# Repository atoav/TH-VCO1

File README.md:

# TH-VCO1

This is a fork based on [the Eurorack Layout Tom Whitwell]( http://www.birthofasynth.com/Thomas_Henry/Pages/VCO-1.html) Oscillator published for the [Thomas Henry VCO 1](http://www.birthofasynth.com/Thomas_Henry/Pages/VCO-1.html) Oscillator.

**NB: All rights to this design rest with Thomas Henry. I do not claim or grant any copyright or license to this design. This is the outcome of an University course at HFBK Hamburg. A limited run of 100 pieces has been produced, which will be sold. We are not allowed to share CAD files of the circuit as "Thomas Henry prefers that all hardware for my designs come from Fonik only, and that schematics for his designs come from Scott and E-M". I will take this page down if he asks me to.** 

## Changes

Compared to Tom's Layout some things changed:

- the complete panel layout has been changed for a fancier (and imho a bit more easier to grasp) layout
- The board-pot has been completely rerouted and is now a single layer board (the bottom layer is a nice, undivided ground plane)
- Two 1x5 Header Pin Strips have been added (this could potentially help to save the screws and add mechanical stability)
- All Resistor Pads have been swapped for square pads
- The PWM CV Attenuator Pot is now a 9mm Alpha trimmer (the small ones with the plastic head, commonly used for attenuverters)
- Cleaned up traces and silkscreen where necessary

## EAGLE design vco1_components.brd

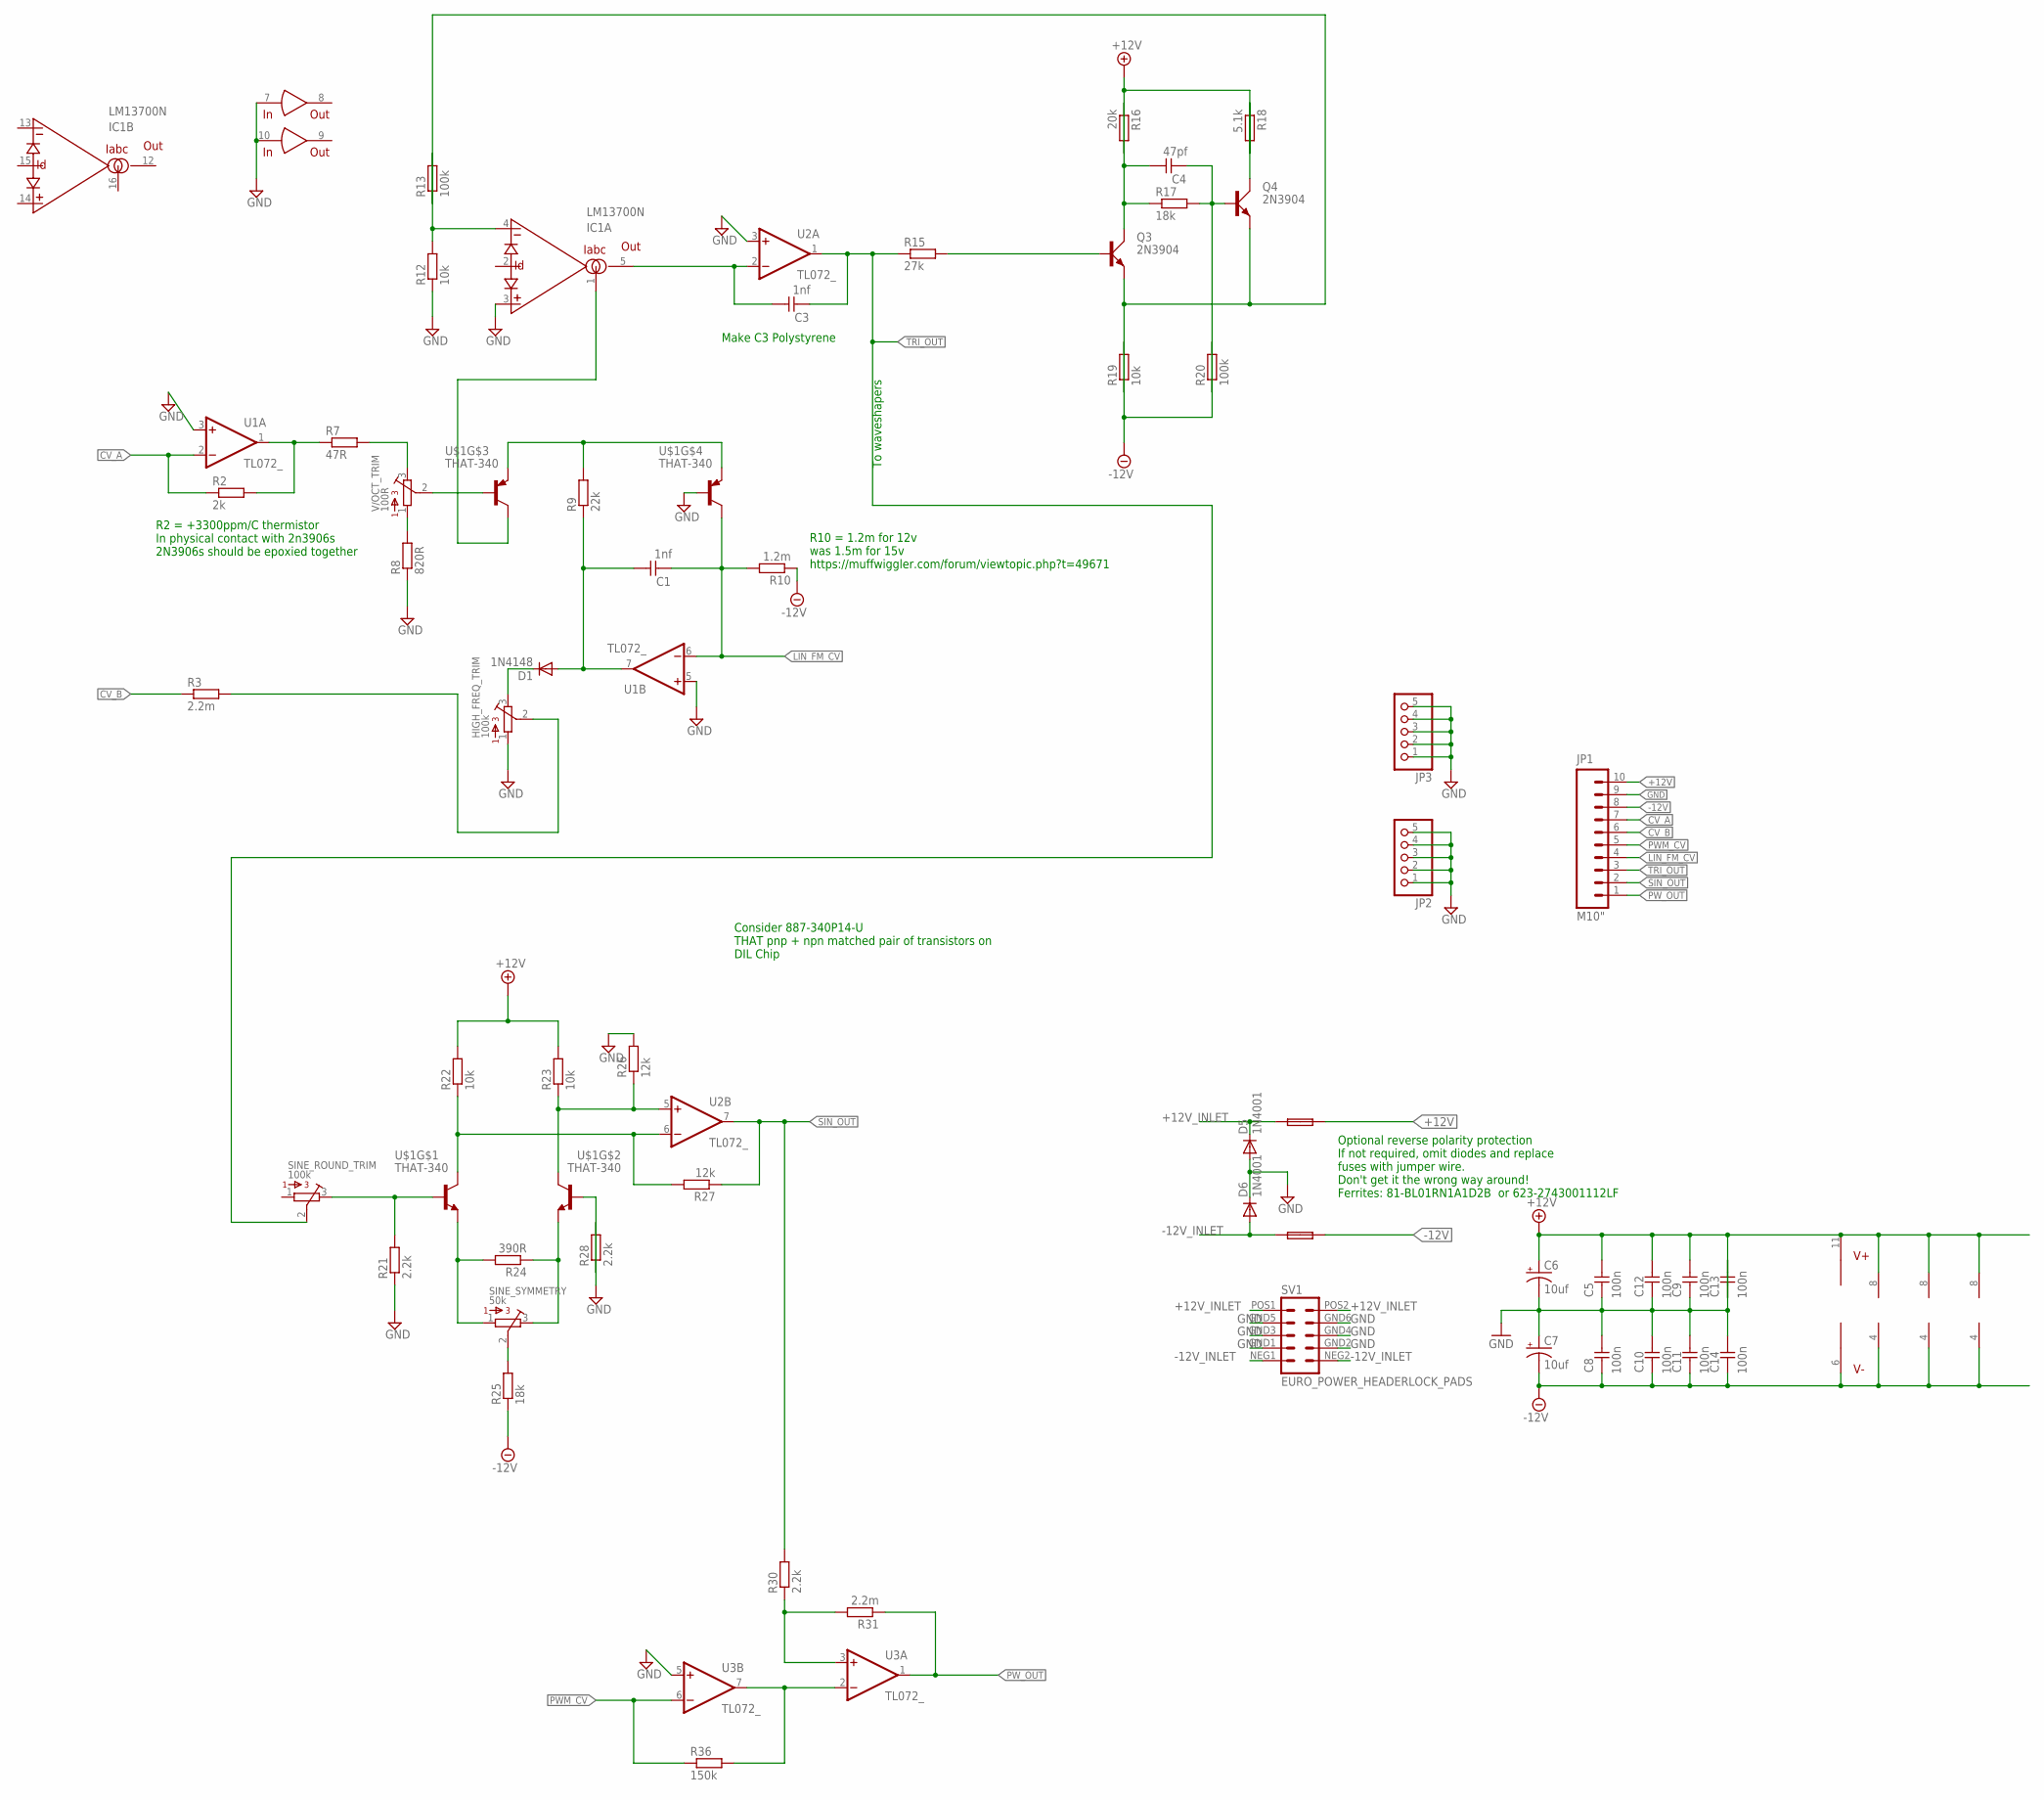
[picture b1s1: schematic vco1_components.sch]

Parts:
C1, C3: 1nf; C050-024X044
C4: 47pf; C050-024X044
C5, C8, C9, C10, C11, C12, C13, C14: 100n; C050-024X044
C6, C7: 10uf; CPOL-RADIAL-10UF-25V
D1: 1N4148; DO35-7
D5, D6: 1N4001; DO41-10
F1, F2: FUSE; C050H075X075
HIGH_FREQ_TRIM: 100k; BOURNS_3362P_TRIMMER
IC1: LM13700N; DIL16
JP1: M10"; 1X10
JP2, JP3: PINHD-1X55X2MM; 1_05X2MM
Q3, Q4: 2N3904; TO92D
R2: 2k; 7MM_RESISTOR
R3, R31: 2.2m; 7MM_RESISTOR
R7: 47R; 7MM_RESISTOR
R8: 820R; 7MM_RESISTOR
R9: 22k; 7MM_RESISTOR
R10: 1.2m; 7MM_RESISTOR
R12, R19, R22, R23: 10k; 7MM_RESISTOR
R13, R20: 100k; 7MM_RESISTOR
R15: 27k; 7MM_RESISTOR
R16: 20k; 7MM_RESISTOR
R17, R25: 18k; 7MM_RESISTOR
R18: 5.1k; 7MM_RESISTOR
R21, R28, R30: 2.2k; 7MM_RESISTOR
R24: 390R; 7MM_RESISTOR
R26, R27: 12k; 7MM_RESISTOR
R36: 150k; 7MM_RESISTOR
SINE_ROUND_TRIM: 100k; BOURNS_3362P_TRIMMER
SINE_SYMMETRY: 50k; BOURNS_3362P_TRIMMER
SV1: EURO_POWER_HEADERLOCK_PADS; EURO_PWR_HEADER_LOCK
U1, U2, U3: TL072_; DIL08
U$1: THAT-340; DIL14
V/OCT_TRIM: 100R; BOURNS_3362P_TRIMMER

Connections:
+12V: C5.1, C6.1 (+), C9.1, C12.1, C13.2, F1.2, IC1.11 (V+), JP1.10, R16.2, R18.2, R22.2, R23.2, U1.8 (V+), U2.8 (V+), U3.8 (V+)
+12V_INLET: D5.C, F1.1, SV1.POS1 (10), SV1.POS2 (9)
-12V: C7.2 (-), C8.2, C10.2, C11.2, C14.2, F2.2, IC1.6 (V-), JP1.8, R10.1, R19.2, R20.2, R25.1, U1.4 (V-), U2.4 (V-), U3.4 (V-)
-12V_INLET: D6.A, F2.1, SV1.NEG1 (2), SV1.NEG2 (1)
CV_A: JP1.7, R2.1, U1.2 (-IN)
CV_B: JP1.6, R3.1
GND: C5.2, C6.2 (-), C7.1 (+), C8.1, C9.2, C10.1, C11.1, C12.2, C13.1, C14.1, D5.A, D6.C, HIGH_FREQ_TRIM.1, IC1.3 (+IN), IC1.7 (IN), IC1.10 (IN), JP1.9, JP2.1, JP2.2, JP2.3, JP2.4, JP2.5, JP3.1, JP3.2, JP3.3, JP3.4, JP3.5, R8.1, R12.1, R21.1, R26.2, R28.2, SV1.GND1 (4), SV1.GND2 (3), SV1.GND3 (6), SV1.GND4 (5), SV1.GND5 (8), SV1.GND6 (7), U1.3 (+IN), U1.5 (+IN), U2.3 (+IN), U3.5 (+IN), U$1.9 (B)
LIN_FM_CV: C1.2, JP1.4, R10.2, U1.6 (-IN), U$1.8 (C)
unnamed: R2.2, R7.1, U1.1 (OUT)
unnamed: R7.2, V/OCT_TRIM.3
unnamed: R8.2, V/OCT_TRIM.1
unnamed: U$1.6 (B), V/OCT_TRIM.2
unnamed: R9.2, U$1.5 (E), U$1.10 (E)
unnamed: IC1.1 (IABC), U$1.7 (C)
unnamed: C1.1, D1.A, R9.1, U1.7 (OUT)
unnamed: D1.C, HIGH_FREQ_TRIM.3
unnamed: HIGH_FREQ_TRIM.2, R3.2
unnamed: IC1.4 (-IN), R12.2, R13.2
unnamed: C3.1, IC1.5 (OUT), U2.2 (-IN)
unnamed: Q3.B, R15.2
unnamed: C4.1, Q3.C, R16.1, R17.1
unnamed: R21.2, SINE_ROUND_TRIM.3, U$1.2 (B)
unnamed: C4.2, Q4.B, R17.2, R20.1
unnamed: Q4.C, R18.1
unnamed: R25.2, SINE_SYMMETRY.2
unnamed: Q3.E, Q4.E, R13.1, R19.1
unnamed: R22.1, R27.2, U2.6 (-IN), U$1.1 (C)
unnamed: R23.1, R26.1, U2.5 (+IN), U$1.14 (C)
unnamed: R24.2, SINE_SYMMETRY.1, U$1.3 (E)
unnamed: R24.1, SINE_SYMMETRY.3, U$1.12 (E)
unnamed: R28.1, U$1.13 (B)
unnamed: R30.1, R31.2, U3.3 (+IN)
unnamed: R36.2, U3.2 (-IN), U3.7 (OUT)
PWM_CV: JP1.5, R36.1, U3.6 (-IN)
PW_OUT: JP1.1, R31.1, U3.1 (OUT)
SIN_OUT: JP1.2, R27.1, R30.2, U2.7 (OUT)
TRI_OUT: C3.2, JP1.3, R15.1, SINE_ROUND_TRIM.2, U2.1 (OUT)

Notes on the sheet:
To waveshapers
R2 = +3300ppm/C thermistor In physical contact with 2n3906s 2N3906s should be epoxied together
Make C3 Polystyrene
R10 = 1.2m for 12v was 1.5m for 15v https://muffwiggler.com/forum/viewtopic.php?t=49671
Consider 887-340P14-U THAT pnp + npn matched pair of transistors on DIL Chip
Optional reverse polarity protection If not required, omit diodes and replace fuses with jumper wire. Don't get it the wrong way around! Ferrites: 81-BL01RN1A1D2B or 623-2743001112LF

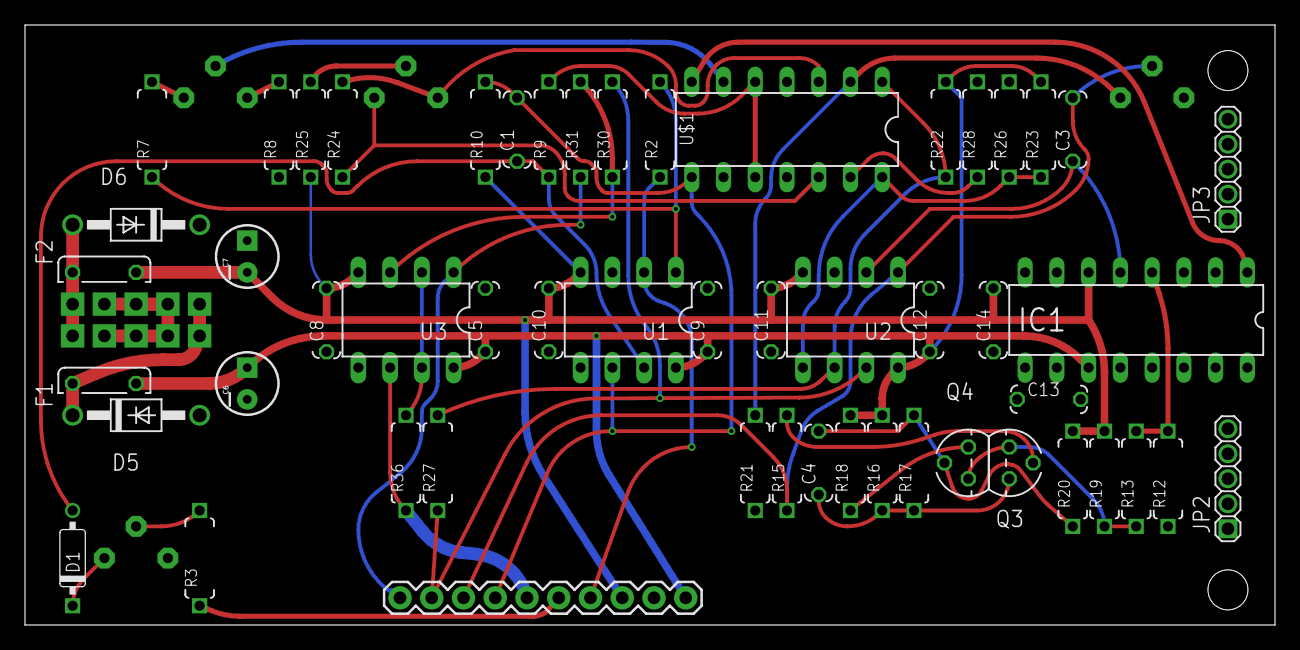
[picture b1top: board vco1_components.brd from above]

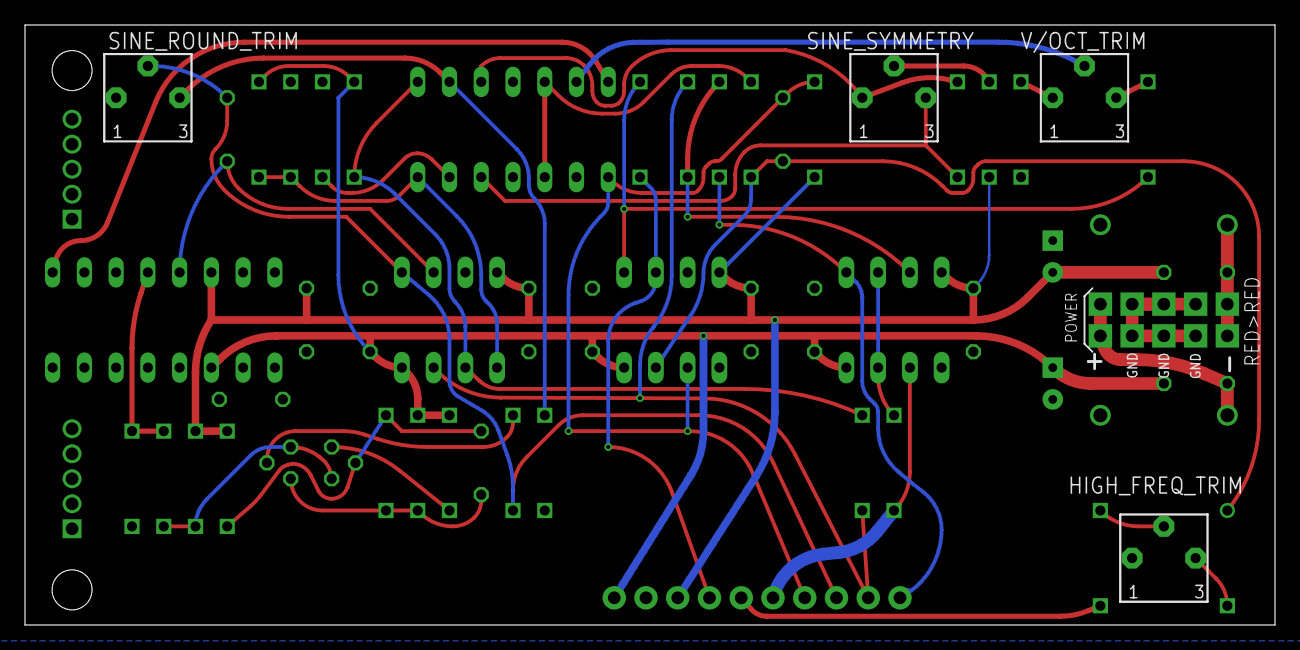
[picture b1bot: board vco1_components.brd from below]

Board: 2 copper layers, 100.0 x 48.0 mm, 58 parts (5 on the bottom side), 37 nets.

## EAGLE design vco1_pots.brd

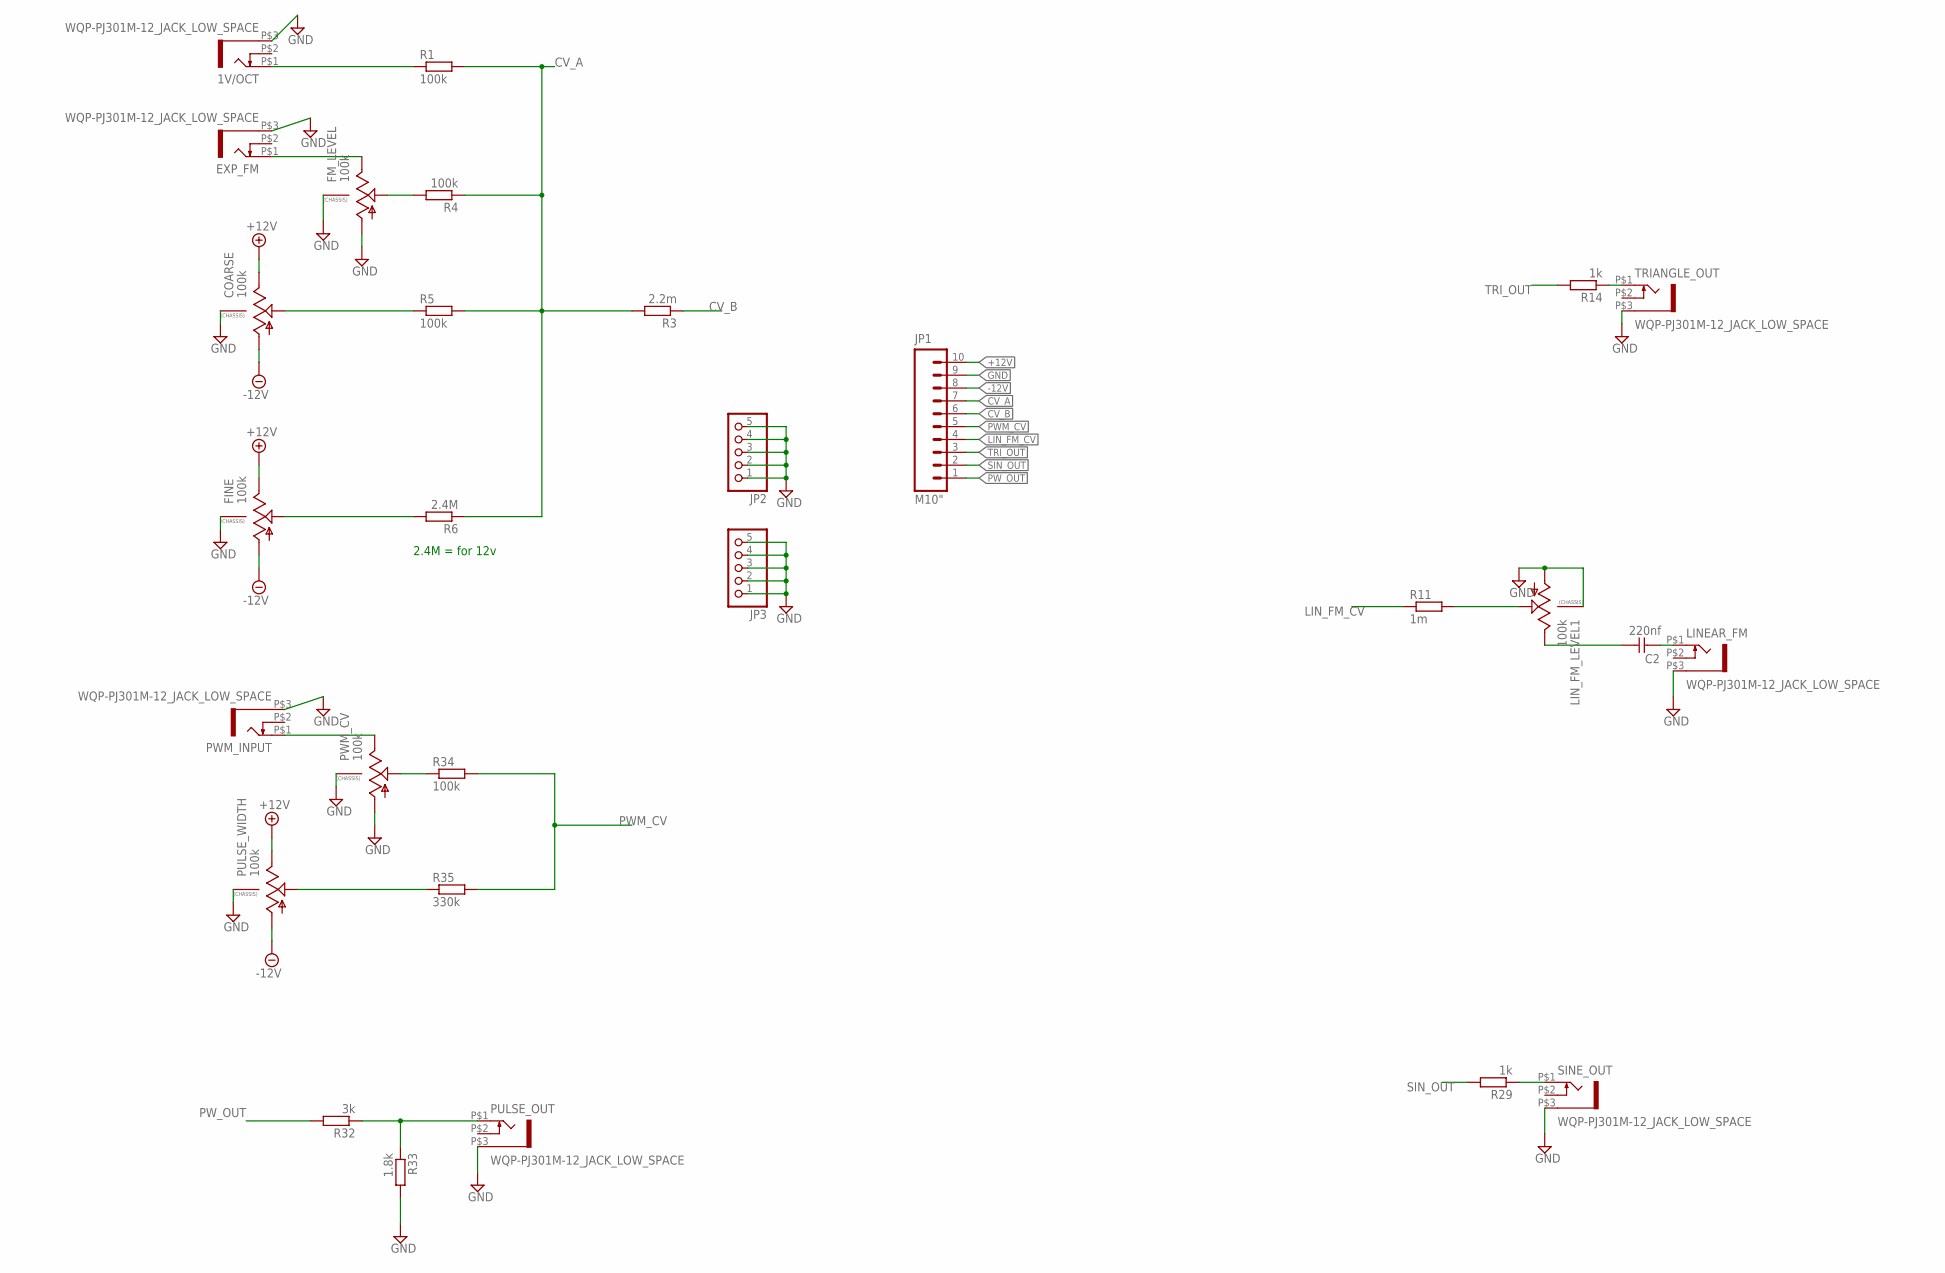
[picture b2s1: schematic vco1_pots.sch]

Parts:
1V/OCT: WQP-PJ301M-12_JACK_LOW_SPACE
C2: 220nf; C050-024X044
COARSE: 100k; 9MM_SNAP-IN_POT
EXP_FM: WQP-PJ301M-12_JACK_LOW_SPACE
FINE: 100k; 9MM_SNAP-IN_POT
FM_LEVEL: 100k; 9MM_SNAP-IN_POT
JP1: M10"; 1X10
JP2, JP3: PINHD-1X55X2MM; 1_05X2MM
LINEAR_FM: WQP-PJ301M-12_JACK_LOW_SPACE
LIN_FM_LEVEL1: 100k; 9MM_SNAP-IN_POT
PULSE_OUT: WQP-PJ301M-12_JACK_LOW_SPACE
PULSE_WIDTH: 100k; 9MM_SNAP-IN_POT
PWM_CV: 100k; 9MM_SNAP-IN_POT
PWM_INPUT: WQP-PJ301M-12_JACK_LOW_SPACE
R1, R4, R5, R34: 100k; 7MM_RESISTOR
R3: 2.2m; 7MM_RESISTOR
R6: 2.4M; 7MM_RESISTOR
R11: 1m; 7MM_RESISTOR
R14, R29: 1k; 7MM_RESISTOR
R32: 3k; 7MM_RESISTOR
R33: 1.8k; 7MM_RESISTOR
R35: 330k; 7MM_RESISTOR
SINE_OUT: WQP-PJ301M-12_JACK_LOW_SPACE
TRIANGLE_OUT: WQP-PJ301M-12_JACK_LOW_SPACE

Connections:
+12V: COARSE.3 (E), FINE.3 (E), JP1.10, PULSE_WIDTH.3 (E)
-12V: COARSE.1 (A), FINE.1 (A), JP1.8, PULSE_WIDTH.1 (A)
CV_A: JP1.7, R1.2, R3.2, R4.1, R5.2, R6.1
CV_B: JP1.6, R3.1
GND: 1V/OCT.P$3 (1), COARSE.CHASSIS2, EXP_FM.P$3 (1), FINE.CHASSIS2, FM_LEVEL.1 (A), FM_LEVEL.CHASSIS2, JP1.9, JP2.1, JP2.2, JP2.3, JP2.4, JP2.5, JP3.1, JP3.2, JP3.3, JP3.4, JP3.5, LINEAR_FM.P$3 (1), LIN_FM_LEVEL1.1 (A), LIN_FM_LEVEL1.CHASSIS2, PULSE_OUT.P$3 (1), PULSE_WIDTH.CHASSIS2, PWM_CV.1 (A), PWM_CV.CHASSIS2, PWM_INPUT.P$3 (1), R33.2, SINE_OUT.P$3 (1), TRIANGLE_OUT.P$3 (1)
LIN_FM_CV: JP1.4, R11.1
unnamed: 1V/OCT.P$1 (2), R1.1
unnamed: EXP_FM.P$1 (2), FM_LEVEL.3 (E)
unnamed: FM_LEVEL.2 (S), R4.2
unnamed: COARSE.2 (S), R5.1
unnamed: FINE.2 (S), R6.2
unnamed: LIN_FM_LEVEL1.2 (S), R11.2
unnamed: R14.1, TRIANGLE_OUT.P$1 (2)
unnamed: C2.1, LIN_FM_LEVEL1.3 (E)
unnamed: C2.2, LINEAR_FM.P$1 (2)
unnamed: R29.1, SINE_OUT.P$1 (2)
unnamed: PULSE_OUT.P$1 (2), R32.1, R33.1
unnamed: PWM_CV.3 (E), PWM_INPUT.P$1 (2)
unnamed: PWM_CV.2 (S), R34.1
unnamed: PULSE_WIDTH.2 (S), R35.1
PWM_CV: JP1.5, R34.2, R35.2
PW_OUT: JP1.1, R32.2
SIN_OUT: JP1.2, R29.2
TRI_OUT: JP1.3, R14.2

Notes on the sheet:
2.4M = for 12v

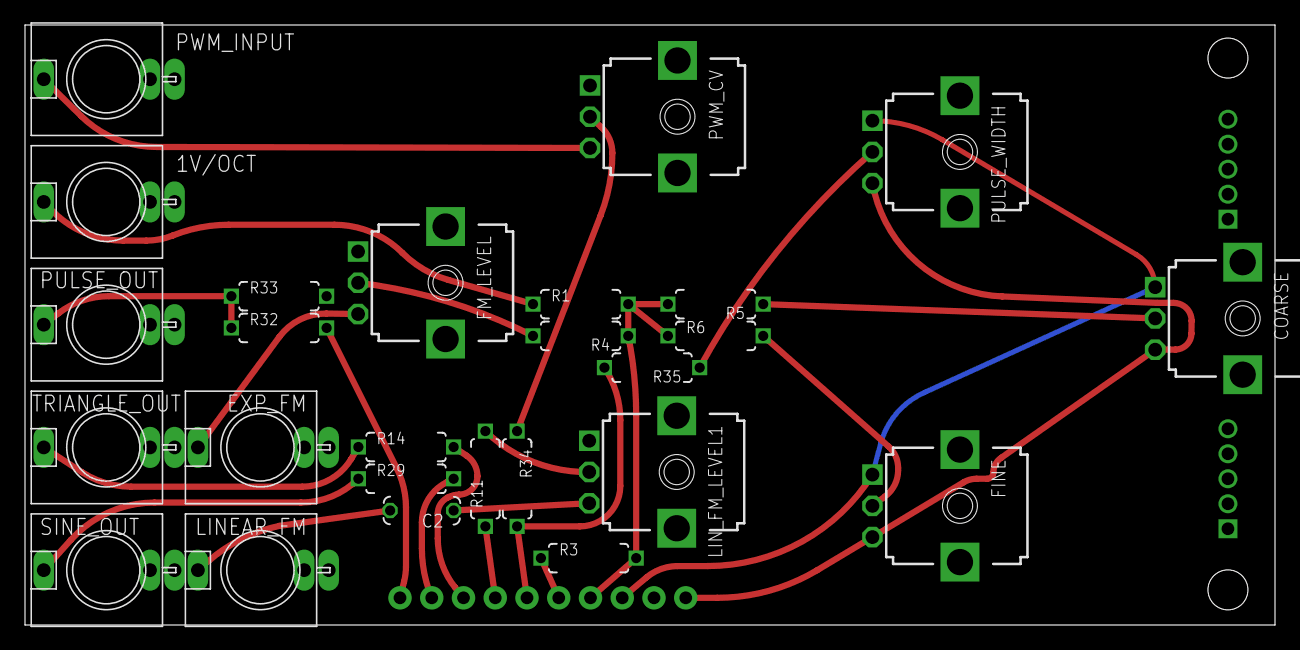
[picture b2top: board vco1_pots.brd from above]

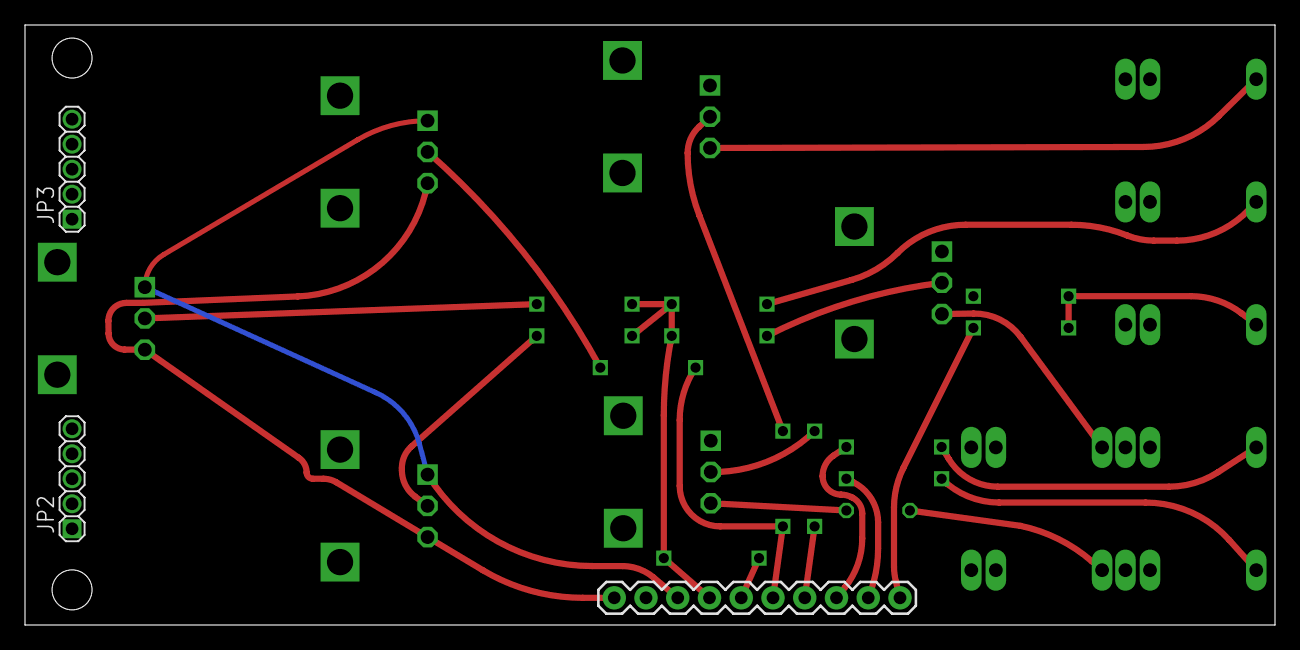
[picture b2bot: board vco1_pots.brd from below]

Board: 2 copper layers, 100.0 x 48.0 mm, 31 parts (3 on the bottom side), 24 nets.

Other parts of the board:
U$2, U$3: MOUNTING_HOLE

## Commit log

2016-11-20 Massive Changes, See Readme
2016-11-20 Correction in the Readme
2016-11-20 Added Image to Readme
2016-11-24 Changed Image Scale
2016-11-24 Minor Changes
2016-11-24 Again Image Stuff
2016-11-24 Scale Image size
2016-11-25 Changed PCB Size, Moved Frequency Knob
    Adapted PCB Boards for the (cheaper) size of 100x49mm which allows two
    PCBs on one 100x100mm Panel. Frequency Pot had to be moved X -1mm
2016-11-25 Fixed small Clearance Problems
2016-11-28 Cleanup of the Board schematics

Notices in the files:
parts and their libraries:
SparkFun-Passives: Licensing: CC v3.0 Share-Alike You are welcome to use this library for commercial purposes.
